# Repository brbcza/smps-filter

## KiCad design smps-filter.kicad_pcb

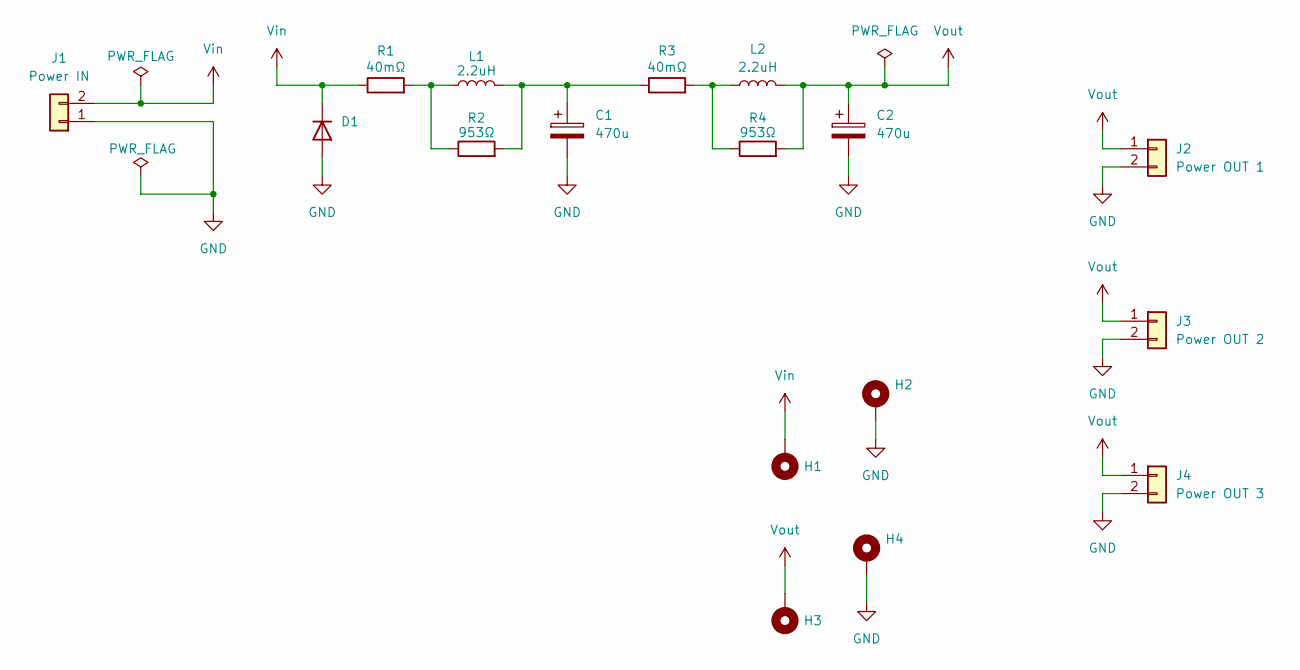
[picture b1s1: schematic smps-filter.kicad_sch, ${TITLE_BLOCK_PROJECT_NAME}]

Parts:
C1, C2: 470u; CP_Elec_10x10.5
D1: P6SMB68A; DO214AA
H1, H2, H3, H4: MountingHole_Pad; MountingHole_2.2mm_M2_DIN965_Pad_TopBottom
J1: Power IN; TerminalBlock_1x02_P7.50mm_Horizontal
J2: Power OUT 1; TerminalBlock_1x02_P7.50mm_Horizontal
J3: Power OUT 2; JST_XH_B2B-XH-A_1x02_P2.50mm_Vertical
J4: Power OUT 3; JST_XH_B2B-XH-A_1x02_P2.50mm_Vertical
L1, L2: 2.2uH; L_10.4x10.4_H4.8
R1, R3: 40mΩ; R_2512_6332Metric_Pad1.40x3.35mm_HandSolder
R2, R4: 953Ω; R_2512_6332Metric_Pad1.40x3.35mm_HandSolder

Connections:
GND: C1.2, C2.2, D1.2 (A), H2.1, H4.1, J1.1, J2.2, J3.2, J4.2
unnamed: C1.1, L1.2, R2.2, R3.1
unnamed: L1.1, R1.2, R2.1
unnamed: L2.1, R3.2, R4.1
Vin: D1.1 (K), H1.1, J1.2, R1.1
Vout: C2.1, H3.1, J2.1, J3.1, J4.1, L2.2, R4.2

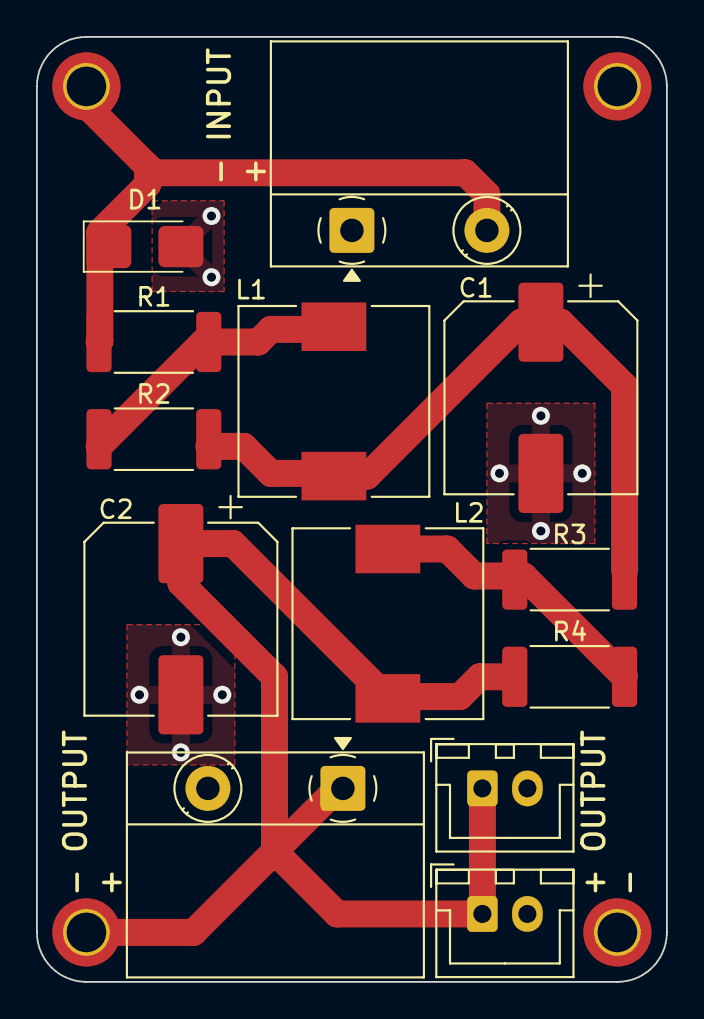
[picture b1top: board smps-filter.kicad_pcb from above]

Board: 2 copper layers, 35.0 x 52.5 mm, 17 parts (1 on the bottom side), 6 nets.

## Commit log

2025-05-02 Added schematics
2025-05-04 Finalied schema and PCB
2025-05-04 Implement GitHub workflows for release and testing
2025-05-04 Fixed DRC errors
2025-05-04 Made round corners
